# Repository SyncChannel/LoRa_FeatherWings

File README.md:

# LoRa_FeatherWings

Custom LoRa FeatherWings for Adafruit Feather

Check out my blog to get full details on these boards.

LoRa FeatherWing Development Breakout:

http://syncchannel.blogspot.com/2016/02/lora-featherwing-development-breakout.html

LoRa FeatherWing IOX:

http://syncchannel.blogspot.com/2016/03/lora-featherwing-iox-for-adafruit.html

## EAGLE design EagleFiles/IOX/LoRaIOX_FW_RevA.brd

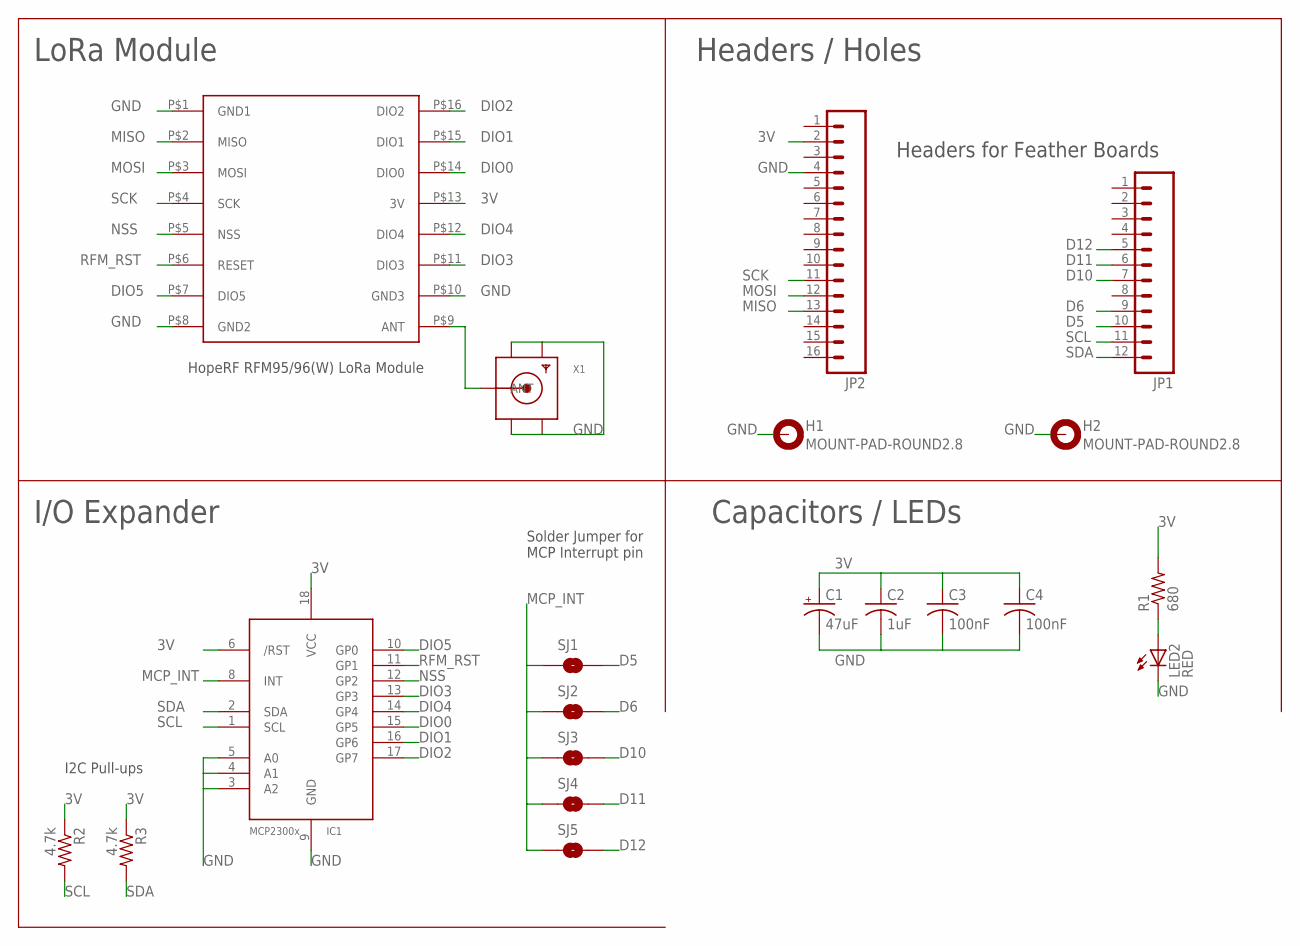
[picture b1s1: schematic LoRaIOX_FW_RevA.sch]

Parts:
C1: 47uF; EIA3528
C2: 1uF; C0603
C3, C4: 100nF; C0603
H1, H2: MOUNT-PAD-ROUND2.8; 2,8-PAD
IC1: MCP2300X/SO; SO18W
JP1: M12NO_SILK; 1X12_NO_SILK
JP2: M161X16_NO_SILK; 1X16_NO_SILK
LED2: RED; CHIPLED_0805
R1: 680; R0603
R2, R3: 4.7k; R0603
SJ1, SJ2, SJ3, SJ4, SJ5: JUMPER-PAD-2-NOYES_SILK; PAD-JUMPER-2-NO_YES_SILK
U$2: RFM95W
X1: SMACONNECTOR_EDGE; SMA_EDGELAUNCH

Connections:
3V: C1.A (+), C2.1, C3.1, C4.1, IC1.6 (/RST), IC1.18 (VCC), JP2.2, R1.2, R2.1, R3.1, U$2.P$13 (3V)
ANT: U$2.P$9 (ANT), X1.P (ANT)
D5: JP1.10, SJ1.2
D6: JP1.9, SJ2.2
D10: JP1.7, SJ3.2
D11: JP1.6, SJ4.2
D12: JP1.5, SJ5.2
DIO0: IC1.15 (GP5), U$2.P$14 (DIO0)
DIO1: IC1.16 (GP6), U$2.P$15 (DIO1)
DIO2: IC1.17 (GP7), U$2.P$16 (DIO2)
DIO3: IC1.13 (GP3), U$2.P$11 (DIO3)
DIO4: IC1.14 (GP4), U$2.P$12 (DIO4)
DIO5: IC1.10 (GP0), U$2.P$7 (DIO5)
GND: C1.C (-), C2.2, C3.2, C4.2, H1.B2,8, H2.B2,8, IC1.3 (A2), IC1.4 (A1), IC1.5 (A0), IC1.9 (GND), JP2.4, LED2.C, U$2.P$1 (GND1), U$2.P$8 (GND2), U$2.P$10 (GND3), X1.GND@1 (GND4), X1.GND@2 (GND3), X1.GND@3 (GND2), X1.GND@4 (GND1)
MCP_INT: IC1.8 (INT), SJ1.1, SJ2.1, SJ3.1, SJ4.1, SJ5.1
MISO: JP2.13, U$2.P$2 (MISO)
MOSI: JP2.12, U$2.P$3 (MOSI)
unnamed: LED2.A, R1.1
NSS: IC1.12 (GP2), U$2.P$5 (NSS)
RFM_RST: IC1.11 (GP1), U$2.P$6 (RESET)
SCK: JP2.11, U$2.P$4 (SCK)
SCL: IC1.1 (SCL), JP1.11, R2.2
SDA: IC1.2 (SDA), JP1.12, R3.2

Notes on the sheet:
Headers for Feather Boards
HopeRF RFM95/96(W) LoRa Module
LoRa Module
Headers / Holes
Capacitors / LEDs
I/O Expander
Solder Jumper for MCP Interrupt pin
I2C Pull-ups

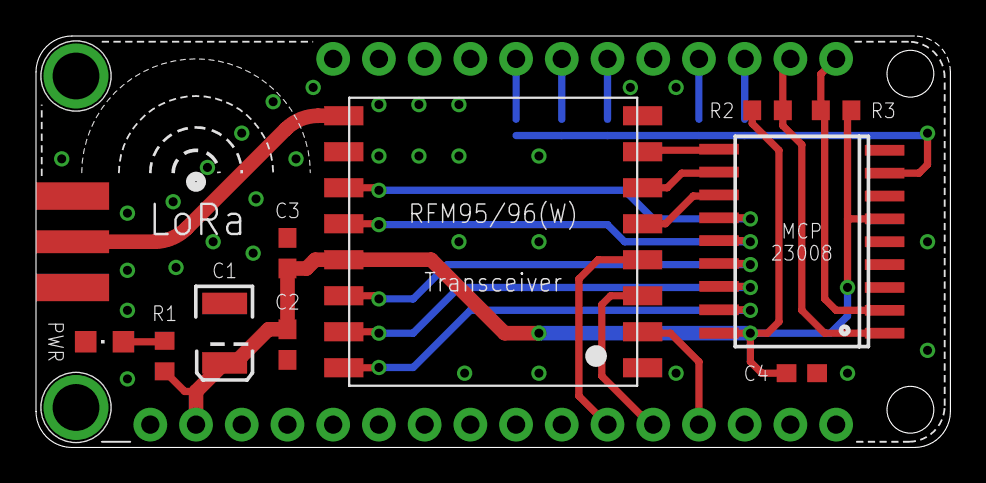
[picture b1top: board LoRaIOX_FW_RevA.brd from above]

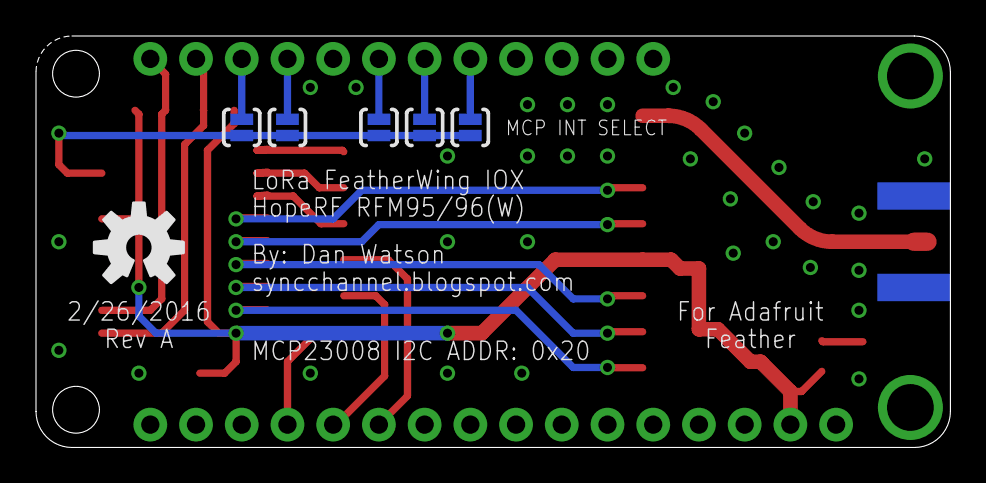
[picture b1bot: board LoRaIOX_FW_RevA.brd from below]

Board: 2 copper layers, 50.8 x 22.9 mm, 21 parts (6 on the bottom side), 23 nets.

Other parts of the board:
U$1: OSHW-LOGO-M

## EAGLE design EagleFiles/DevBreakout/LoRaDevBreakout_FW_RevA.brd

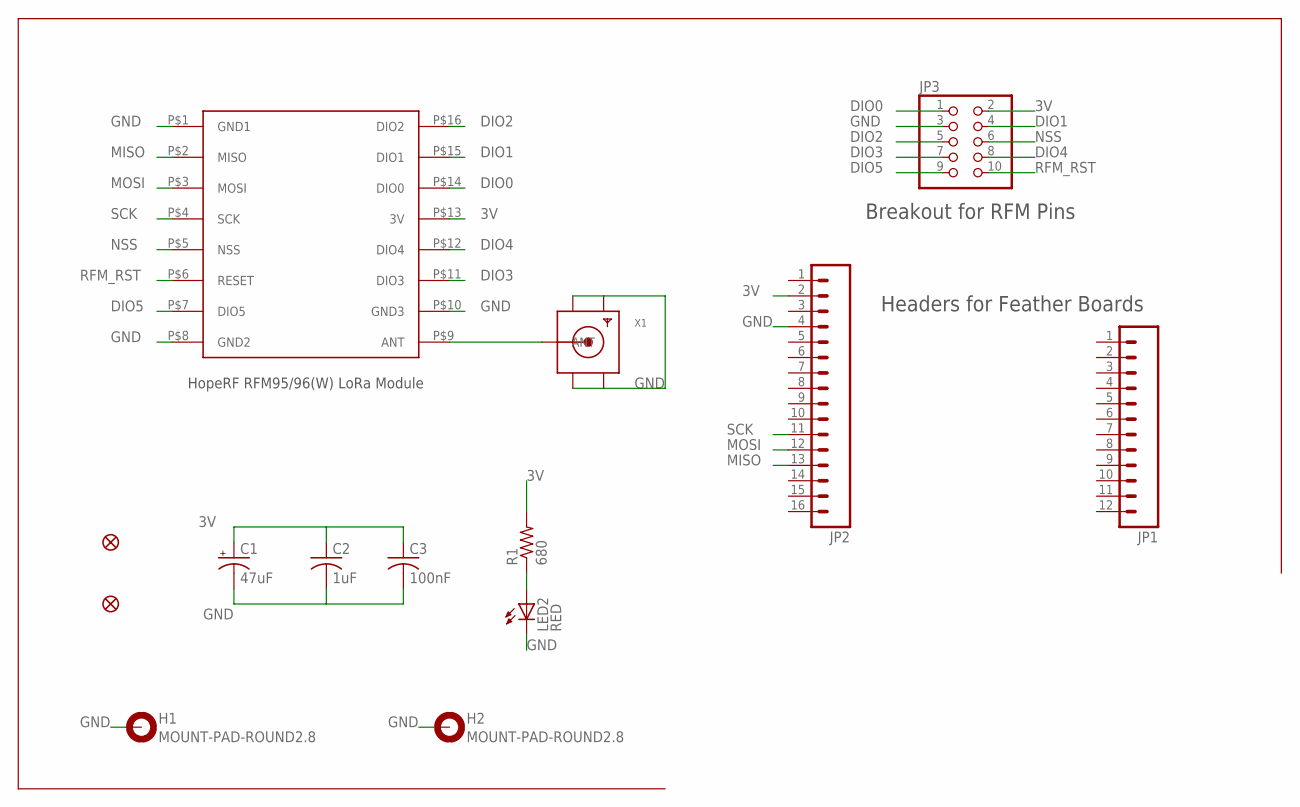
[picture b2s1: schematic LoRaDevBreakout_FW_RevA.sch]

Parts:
C1: 47uF; EIA3528
C2: 1uF; C0603
C3: 100nF; C0603
FID1, FID2: FIDUCIAL1X2; FIDUCIAL-1X2
H1, H2: MOUNT-PAD-ROUND2.8; 2,8-PAD
JP1: M12NO_SILK; 1X12_NO_SILK
JP2: M161X16_NO_SILK; 1X16_NO_SILK
JP3: PINHD-2X5; 2X05
LED2: RED; CHIPLED_0805
R1: 680; R0603
U$2: RFM95W
X1: SMACONNECTOR_EDGE; SMA_EDGELAUNCH

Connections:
3V: C1.A (+), C2.1, C3.1, JP2.2, JP3.2, R1.2, U$2.P$13 (3V)
ANT: U$2.P$9 (ANT), X1.P (ANT)
DIO0: JP3.1, U$2.P$14 (DIO0)
DIO1: JP3.4, U$2.P$15 (DIO1)
DIO2: JP3.5, U$2.P$16 (DIO2)
DIO3: JP3.7, U$2.P$11 (DIO3)
DIO4: JP3.8, U$2.P$12 (DIO4)
DIO5: JP3.9, U$2.P$7 (DIO5)
GND: C1.C (-), C2.2, C3.2, H1.B2,8, H2.B2,8, JP2.4, JP3.3, LED2.C, U$2.P$1 (GND1), U$2.P$8 (GND2), U$2.P$10 (GND3), X1.GND@1 (GND4), X1.GND@2 (GND3), X1.GND@3 (GND2), X1.GND@4 (GND1)
MISO: JP2.13, U$2.P$2 (MISO)
MOSI: JP2.12, U$2.P$3 (MOSI)
unnamed: LED2.A, R1.1
NSS: JP3.6, U$2.P$5 (NSS)
RFM_RST: JP3.10, U$2.P$6 (RESET)
SCK: JP2.11, U$2.P$4 (SCK)

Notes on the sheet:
Headers for Feather Boards
Breakout for RFM Pins
HopeRF RFM95/96(W) LoRa Module

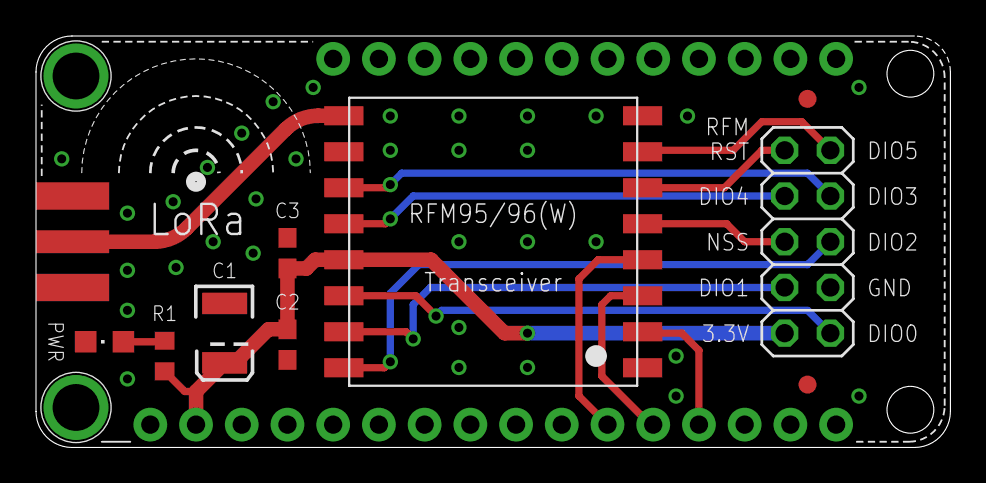
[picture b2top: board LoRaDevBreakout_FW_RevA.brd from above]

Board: 2 copper layers, 50.8 x 22.9 mm, 15 parts (1 on the bottom side), 15 nets.

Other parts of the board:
U$1: OSHW-LOGO-M

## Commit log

2016-04-25 :octocat: Added .gitattributes & .gitignore files
2016-04-25 Revert ":octocat: Added .gitattributes & .gitignore files"
    This reverts commit 5010c75730f6d0c12c55f09ad05a37bd327a3561.
2016-04-25 Added Eagle files

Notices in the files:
parts and their libraries:
SparkFun-Connectors: Licensing: Creative Commons ShareAlike 4.0 International - https://creativecommons.org/licenses/by-sa/4.0
